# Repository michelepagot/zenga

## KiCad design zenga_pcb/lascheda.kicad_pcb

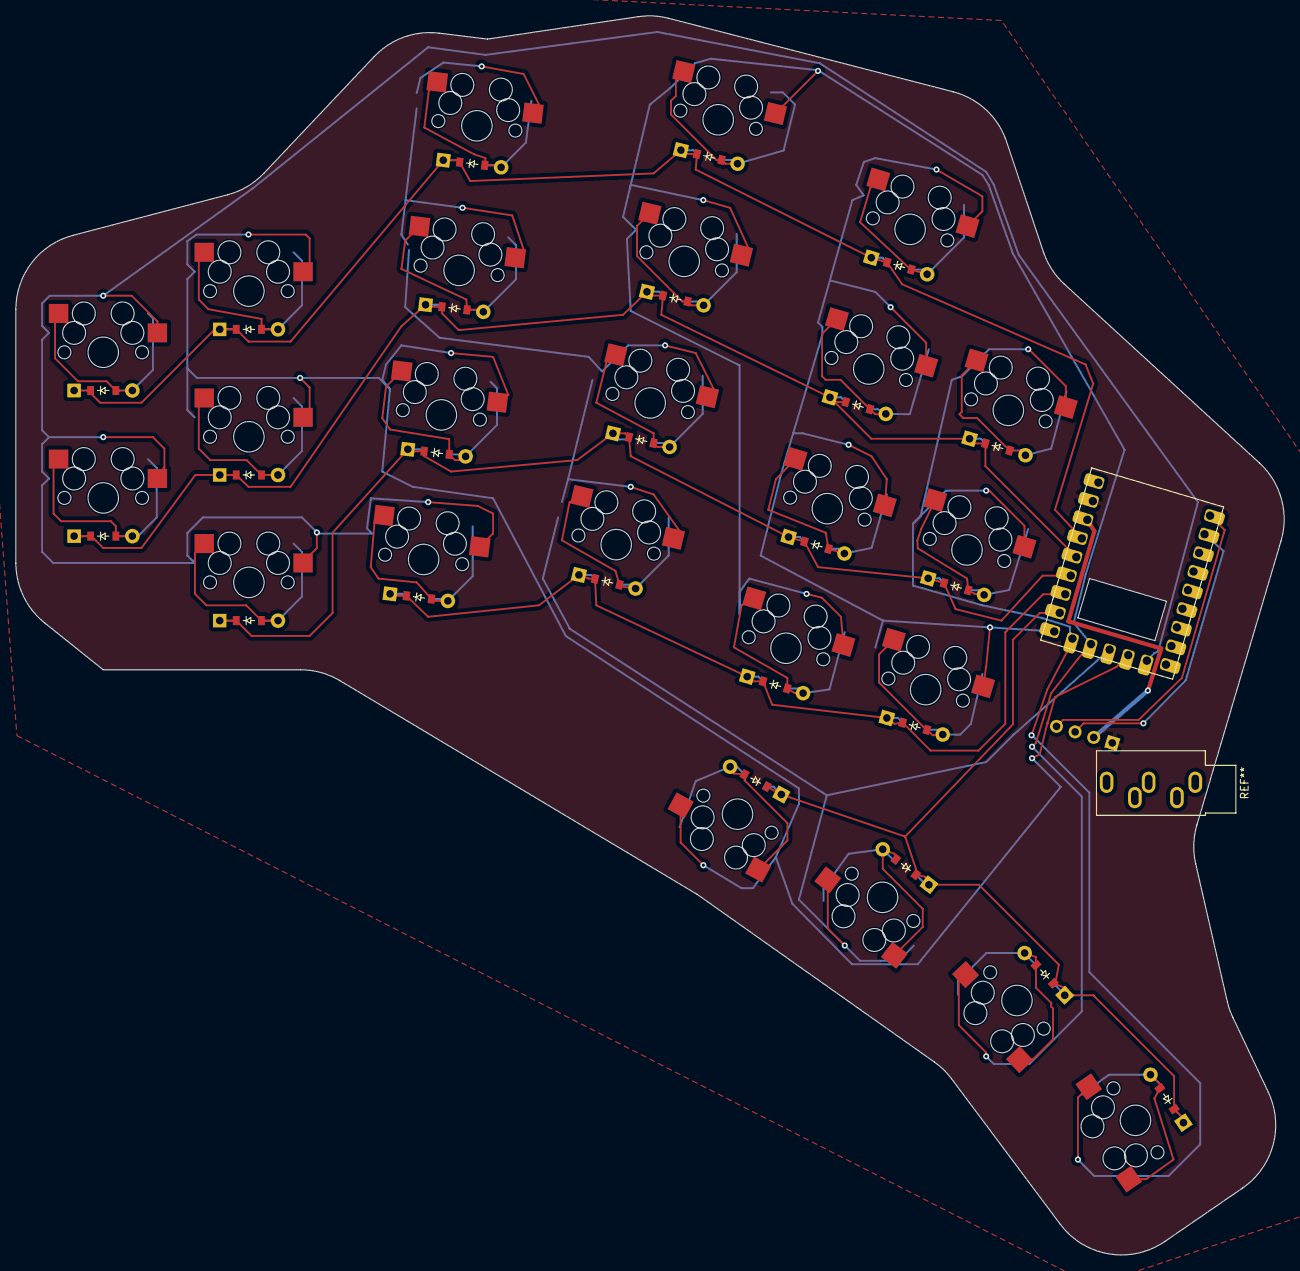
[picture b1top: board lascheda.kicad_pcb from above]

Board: 2 copper layers, 165.9 x 162.1 mm, 50 parts (0 on the bottom side), 39 nets.

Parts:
D1, D2, D3, D4, D5, D6, D7, D8, D9, D10, D11, D12, D13, D14, D15, D16, D17, D18, D19, D20, D21, D22, D23, D24: ComboDiode
OLED1: OLED; OLED_headers
RP2040Zero1: RP2040-Zero
S1, S2, S3, S4, S5, S6, S7, S8, S9, S10, S11, S12, S13, S14, S15, S16, S17, S18, S19, S20, S21, S22, S23, S24: MX

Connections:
GND: OLED1.1, RP2040Zero1.20
GP0: OLED1.4, RP2040Zero1.1
GP1: OLED1.3, RP2040Zero1.2
GP9: RP2040Zero1.10, S1.1, S2.1, S3.1, S6.1
GP10: RP2040Zero1.11, S4.1, S5.1, S7.1, S21.1
GP11: RP2040Zero1.12, S8.1, S9.1, S10.1, S11.1, S22.1
GP12: RP2040Zero1.13, S12.1, S13.1, S14.1, S23.1
GP13: RP2040Zero1.14, S19.1, S20.1, S24.1
GP14: RP2040Zero1.15, S15.1, S16.1, S17.1, S18.1
GP15: D21.1, D22.1, D23.1, D24.1, RP2040Zero1.16
GP26: D6.1, D10.1, D14.1, D18.1, RP2040Zero1.17
GP27: D3.1, D7.1, D11.1, D15.1, D19.1, RP2040Zero1.18
GP28: D1.1, D4.1, D8.1, D12.1, D16.1, D20.1, RP2040Zero1.22
GP29: D2.1, D5.1, D9.1, D13.1, D17.1, RP2040Zero1.23
P3V3: OLED1.2, RP2040Zero1.21
indexinner_bottom: D19.2, S19.2
indexinner_home: D20.2, S20.2
indexinner_mod: D18.2, S18.2
indexouter_bottom: D15.2, S15.2
indexouter_home: D16.2, S16.2
indexouter_mod: D14.2, S14.2
indexouter_top: D17.2, S17.2
middlemain_bottom: D11.2, S11.2
middlemain_home: D12.2, S12.2
middlemain_mod: D10.2, S10.2
middlemain_top: D13.2, S13.2
pinkyinner_bottom: D3.2, S3.2
pinkyinner_home: D4.2, S4.2
pinkyinner_top: D5.2, S5.2
pinkyouter_home: D1.2, S1.2
pinkyouter_top: D2.2, S2.2
ringmain_bottom: D7.2, S7.2
ringmain_home: D8.2, S8.2
ringmain_mod: D6.2, S6.2
ringmain_top: D9.2, S9.2
thumbmain_thumbinner: D22.2, S22.2
thumbmain_thumbmoreinner: D21.2, S21.2
thumbmain_thumbmoreouter: D24.2, S24.2
thumbmain_thumbouter: D23.2, S23.2

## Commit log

2024-08-07 Parametric board
2024-08-07 Add metadata and make it more parametric
2024-09-02 Start creating the PCB
2024-09-03 Move to rp2040zero
2024-09-03 Start create nets
2024-11-18 Picture of connection matrix
2024-11-19 First zenga routing
2024-11-21 Fix the columns names
2024-11-22 Kicad 8
    Set Kicad 8 template in the ergogen config
    Fix more column overlap names
    Save some images in the repo
    Save a manually crafter PCB KiCAD file
2024-11-22 Finish first routing draft
2024-11-25 End of Hackweek
